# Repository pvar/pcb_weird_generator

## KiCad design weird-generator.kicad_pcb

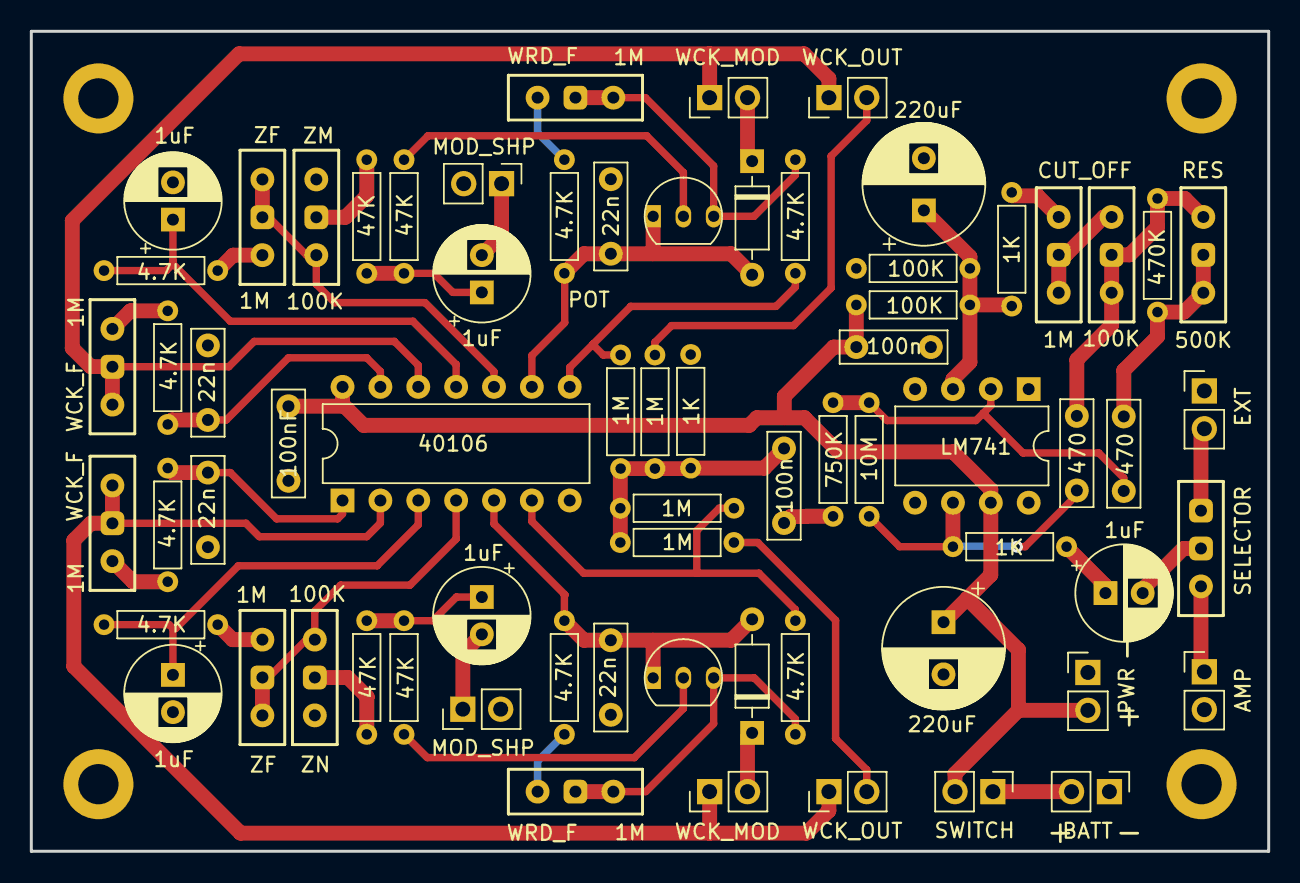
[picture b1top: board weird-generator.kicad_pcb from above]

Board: 2 copper layers, 83.0 x 55.0 mm, 69 parts (0 on the bottom side), 48 nets.

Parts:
C1, C2, C7, C8: 22n; C_Rect_L7.0mm_W2.0mm_P5.00mm
C3, C4, C5, C6, C16: 1uF; CP_Radial_D6.3mm_P2.50mm
C9, C12: 100n; C_Rect_L7.0mm_W2.0mm_P5.00mm
C10: 100nF; C_Rect_L7.0mm_W2.0mm_P5.00mm
C11, C13: 220uF; CP_Radial_D8.0mm_P3.50mm
C14, C15: 470; C_Rect_L7.0mm_W2.0mm_P5.00mm
D1, D2: 1N4148; D_DO-35_SOD27_P7.62mm_Horizontal
J1: BATT; PinHeader_1x02_P2.54mm_Vertical
J2: AMP; PinHeader_1x02_P2.54mm_Vertical
J3: EXT; PinHeader_1x02_P2.54mm_Vertical
MOD_SHP: Unusual; PinHeader_1x02_P2.54mm_Vertical
MOD_SHP#2: Unusual; PinHeader_1x02_P2.54mm_Vertical
Q1, Q2: 2N3904; TO-92_Inline
R1, R2, R3, R4, R9, R10, R11, R12: 4.7K; resistor_fx_footprint
R5, R6, R7, R8: 47K; resistor_fx_footprint
R13, R14, R15, R16: 1M; resistor_fx_footprint
R17, R22, R24: 1K; resistor_fx_footprint
R18: 750K; resistor_fx_footprint
R19, R20: 100K; resistor_fx_footprint
R21: 10M; resistor_fx_footprint
R23: 470K; resistor_fx_footprint
RV1, RV2, RV3, RV4, RV7, RV8, RV9: 1M; potentiometer_fx_connector
RV5, RV6, RV10: 100K; potentiometer_fx_connector
RV11: 500K; potentiometer_fx_connector
SW7: SWITCH; PinHeader_1x02_P2.54mm_Vertical
SW7#2: PWR; PinHeader_1x02_P2.54mm_Vertical
SW8: SELECTOR; switch_fx_connector
U1: 40106; DIP-14_W7.62mm
U3: LM741; DIP-8_W7.62mm
WCK_MOD: Wacky; PinHeader_1x02_P2.54mm_Vertical
WCK_MOD#2: Wacky; PinHeader_1x02_P2.54mm_Vertical
WCK_OUT: Wacky Out; PinHeader_1x02_P2.54mm_Vertical
WCK_OUT#2: Wacky Out; PinHeader_1x02_P2.54mm_Vertical

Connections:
+BATT: C9.1, C10.1, C11.1, R19.1, SW7.2 (B), SW7#2.2 (B), U1.14 (VDD), U3.7 (V+)
-BATT: C1.2, C2.2, C3.2, C4.2, C7.2, C8.2, C9.2, C10.2, C11.2, C13.2, J1.1, J2.2, J3.1, MOD_SHP.2 (B), MOD_SHP#2.2 (B), R17.2, R20.2, RV5.3, RV6.3, SW7#2.1 (A), U1.7 (VSS), U3.4 (V-)
/filter in: C12.1, R13.2, R14.2, R15.2, R16.2, R17.1
/filter_out: C16.2, SW8.2 (B)
unnamed: C1.1, R1.2, U1.1
unnamed: C2.1, R2.2, U1.13
unnamed: C3.1, R3.2, U1.3
unnamed: C4.1, R4.2, U1.11
unnamed: C5.1, R5.2, R6.1
unnamed: C6.1, R7.2, R8.1
unnamed: C12.2, R18.1
unnamed: C14.2, R23.1, RV11.1, RV11.2
unnamed: C15.1, R21.2, R24.1, U3.6
unnamed: C15.2, R23.2, RV10.1, RV10.2, RV11.3
unnamed: C16.1, R24.2
unnamed: C7.1, D1.2 (A), Q1.1 (E), R9.2, U1.5
unnamed: D1.1 (K), WCK_MOD#2.2 (B)
unnamed: C8.1, D2.2 (A), Q2.1 (E), R11.2, U1.9
unnamed: D2.1 (K), WCK_MOD.2 (B)
unnamed: J1.2, SW7.1 (A)
unnamed: J2.1, SW8.3 (C)
unnamed: J3.2, SW8.1 (A)
unnamed: Q1.2 (B), R6.2
unnamed: Q1.3 (C), R10.1, RV7.1, RV7.2
unnamed: Q2.2 (B), R8.2
unnamed: Q2.3 (C), R12.1, RV8.1, RV8.2
unnamed: R1.1, RV1.3
unnamed: R2.1, RV2.3
unnamed: R3.1, RV3.3
unnamed: R4.1, RV4.3
unnamed: R5.1, RV5.2
unnamed: R7.1, RV6.2
unnamed: R9.1, RV7.3
unnamed: R10.2, R13.1, U1.6
unnamed: R11.1, RV8.3
unnamed: R12.2, R16.1, U1.8
unnamed: R22.1, RV9.3
unnamed: RV3.1, RV3.2, RV5.1, U1.4
unnamed: RV4.1, RV4.2, RV6.1, U1.10
unnamed: RV9.1, RV9.2, RV10.3
unnamed: C5.2, MOD_SHP#2.1 (A)
unnamed: C6.2, MOD_SHP.1 (A)
unnamed: RV1.1, RV1.2, U1.2, WCK_MOD#2.1 (A), WCK_OUT#2.1 (A)
unnamed: RV2.1, RV2.2, U1.12, WCK_MOD.1 (A), WCK_OUT.1 (A)
unnamed: R14.1, WCK_OUT#2.2 (B)
unnamed: R15.1, WCK_OUT.2 (B)
unnamed: C13.1, R19.2, R20.1, R22.2, U3.3 (+)
unnamed: C14.1, R18.2, R21.1, U3.2 (-)

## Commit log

2023-12-23 Added schematic
2023-12-24 Initial PCB iteration
2023-12-24 Completed trace routing
2023-12-25 Rearranged components and shrunk board
2023-12-26 Added mounting holes
2023-12-26 Improved component placement
2023-12-27 Added value labels and fixed some component drawings
2023-12-28 Refactored & shrunk board
2025-08-14 Shrunk board (even more)
2025-08-14 Added licence file
2025-08-15 Redesigned to accommodate extra functionality
2025-08-15 Added dual audio output and selector switch
